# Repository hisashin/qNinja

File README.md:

# Open Source $300 Real Time PCR and LAMP machine "qNinja"

# $50 qLAMP machine "[qNinja Lite](https://github.com/hisashin/qNinjaLite)" is also available

## Reference Links
- [qNinja portal](https://qninja.hisa.dev)

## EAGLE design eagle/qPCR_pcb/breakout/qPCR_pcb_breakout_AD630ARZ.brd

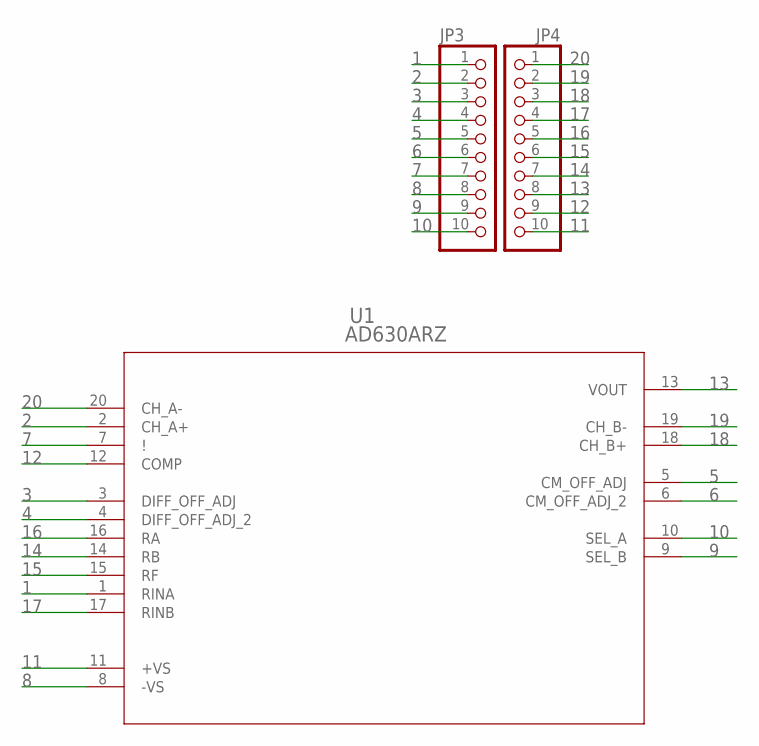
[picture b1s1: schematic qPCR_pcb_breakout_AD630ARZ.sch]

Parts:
JP3, JP4: PINHD-1X10; 1X10
U1: AD630ARZ; RW_20_ADI

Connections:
1: JP3.1, U1.1 (RINA)
2: JP3.2, U1.2 (CH_A+)
3: JP3.3, U1.3 (DIFF_OFF_ADJ)
4: JP3.4, U1.4 (DIFF_OFF_ADJ_2)
5: JP3.5, U1.5 (CM_OFF_ADJ)
6: JP3.6, U1.6 (CM_OFF_ADJ_2)
7: JP3.7, U1.7 (!)
8: JP3.8, U1.8 (-VS)
9: JP3.9, U1.9 (SEL_B)
10: JP3.10, U1.10 (SEL_A)
11: JP4.10, U1.11 (+VS)
12: JP4.9, U1.12 (COMP)
13: JP4.8, U1.13 (VOUT)
14: JP4.7, U1.14 (RB)
15: JP4.6, U1.15 (RF)
16: JP4.5, U1.16 (RA)
17: JP4.4, U1.17 (RINB)
18: JP4.3, U1.18 (CH_B+)
19: JP4.2, U1.19 (CH_B-)
20: JP4.1, U1.20 (CH_A-)

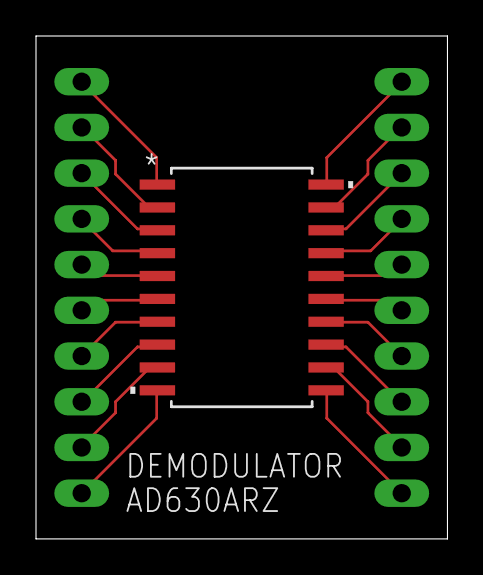
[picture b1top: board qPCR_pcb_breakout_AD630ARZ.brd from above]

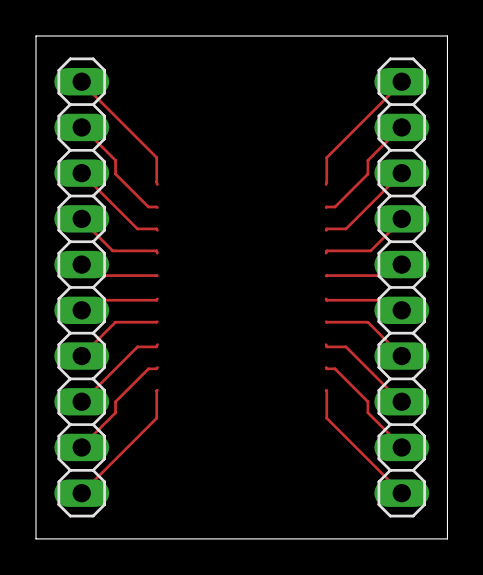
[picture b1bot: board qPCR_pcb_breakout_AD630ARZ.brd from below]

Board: 2 copper layers, 22.9 x 27.9 mm, 3 parts (2 on the bottom side), 20 nets.

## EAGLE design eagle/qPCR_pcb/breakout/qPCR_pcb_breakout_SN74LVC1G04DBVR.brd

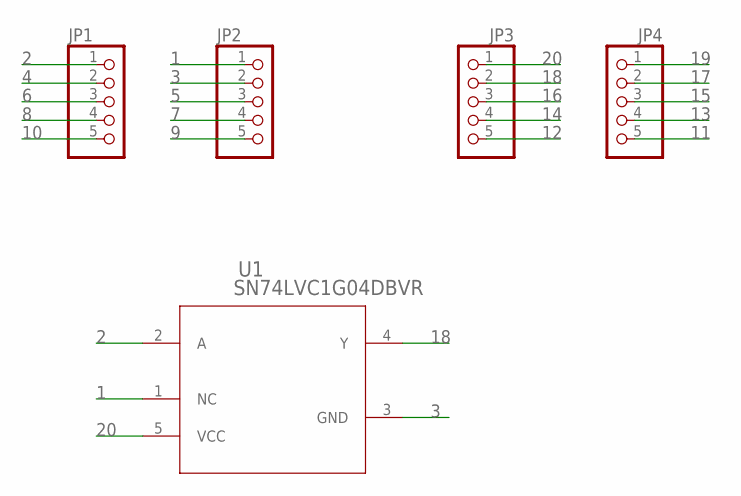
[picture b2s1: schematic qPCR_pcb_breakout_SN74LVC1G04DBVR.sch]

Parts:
JP1, JP2, JP3, JP4: PINHD-1X5R; 1X05R
U1: SN74LVC1G04DBVR; DBV5

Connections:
1: JP2.1, U1.1 (NC)
2: JP1.1, U1.2 (A)
3: JP2.2, U1.3 (GND)
4: JP1.2
5: JP2.3
6: JP1.3
7: JP2.4
8: JP1.4
9: JP2.5
10: JP1.5
11: JP4.5
12: JP3.5
13: JP4.4
14: JP3.4
15: JP4.3
16: JP3.3
17: JP4.2
18: JP3.2, U1.4 (Y)
19: JP4.1
20: JP3.1, U1.5 (VCC)

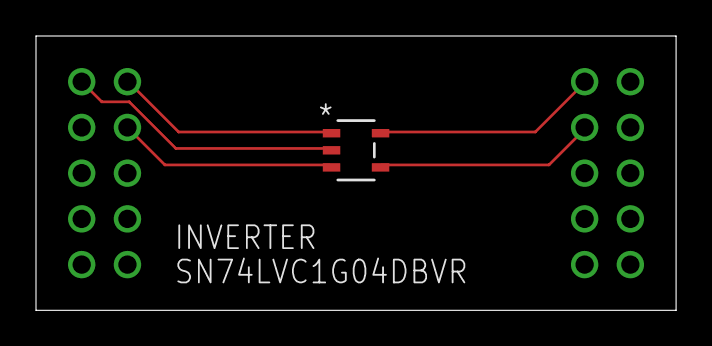
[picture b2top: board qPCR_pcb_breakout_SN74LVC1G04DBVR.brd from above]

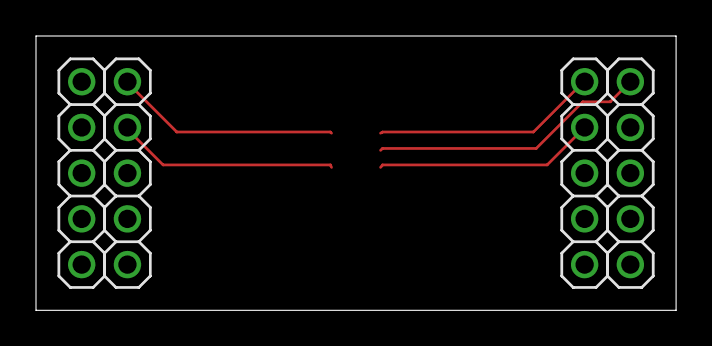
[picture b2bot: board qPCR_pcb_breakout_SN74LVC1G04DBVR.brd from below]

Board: 2 copper layers, 35.6 x 15.2 mm, 5 parts (4 on the bottom side), 5 nets.

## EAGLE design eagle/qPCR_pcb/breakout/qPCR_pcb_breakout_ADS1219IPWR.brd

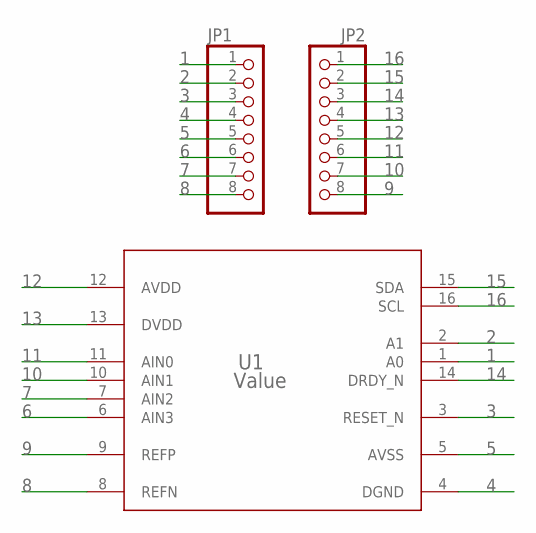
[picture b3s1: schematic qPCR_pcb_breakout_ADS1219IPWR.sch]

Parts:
JP1, JP2: PINHD-1X8; 1X08
U1: Value; PW0016A_N

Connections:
1: JP1.1, U1.1 (A0)
2: JP1.2, U1.2 (A1)
3: JP1.3, U1.3 (RESET_N)
4: JP1.4, U1.4 (DGND)
5: JP1.5, U1.5 (AVSS)
6: JP1.6, U1.6 (AIN3)
7: JP1.7, U1.7 (AIN2)
8: JP1.8, U1.8 (REFN)
9: JP2.8, U1.9 (REFP)
10: JP2.7, U1.10 (AIN1)
11: JP2.6, U1.11 (AIN0)
12: JP2.5, U1.12 (AVDD)
13: JP2.4, U1.13 (DVDD)
14: JP2.3, U1.14 (DRDY_N)
15: JP2.2, U1.15 (SDA)
16: JP2.1, U1.16 (SCL)

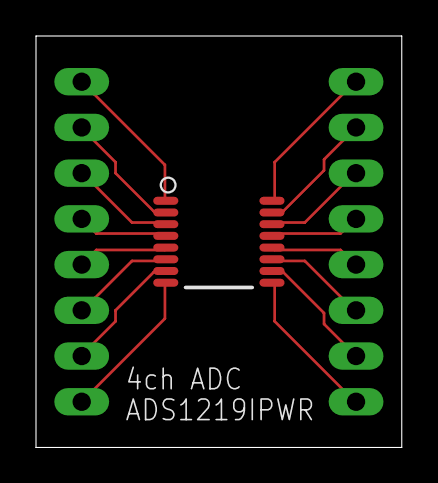
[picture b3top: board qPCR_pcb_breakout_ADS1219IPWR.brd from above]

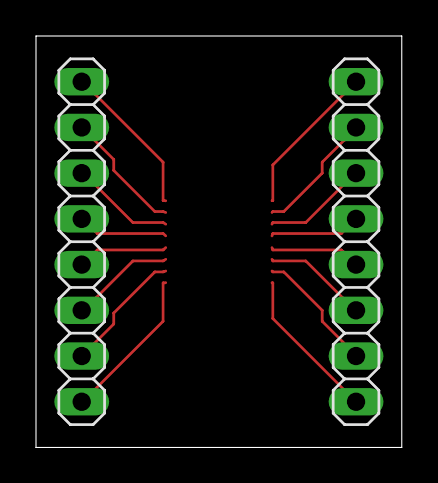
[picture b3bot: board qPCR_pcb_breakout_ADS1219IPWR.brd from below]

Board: 2 copper layers, 20.3 x 22.9 mm, 3 parts (2 on the bottom side), 16 nets.

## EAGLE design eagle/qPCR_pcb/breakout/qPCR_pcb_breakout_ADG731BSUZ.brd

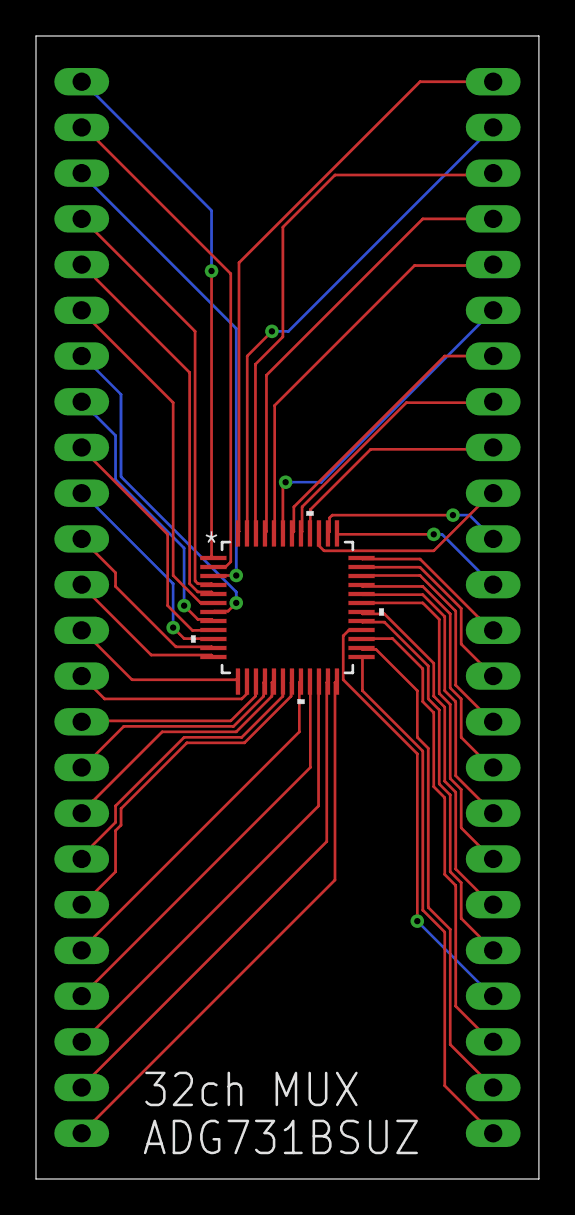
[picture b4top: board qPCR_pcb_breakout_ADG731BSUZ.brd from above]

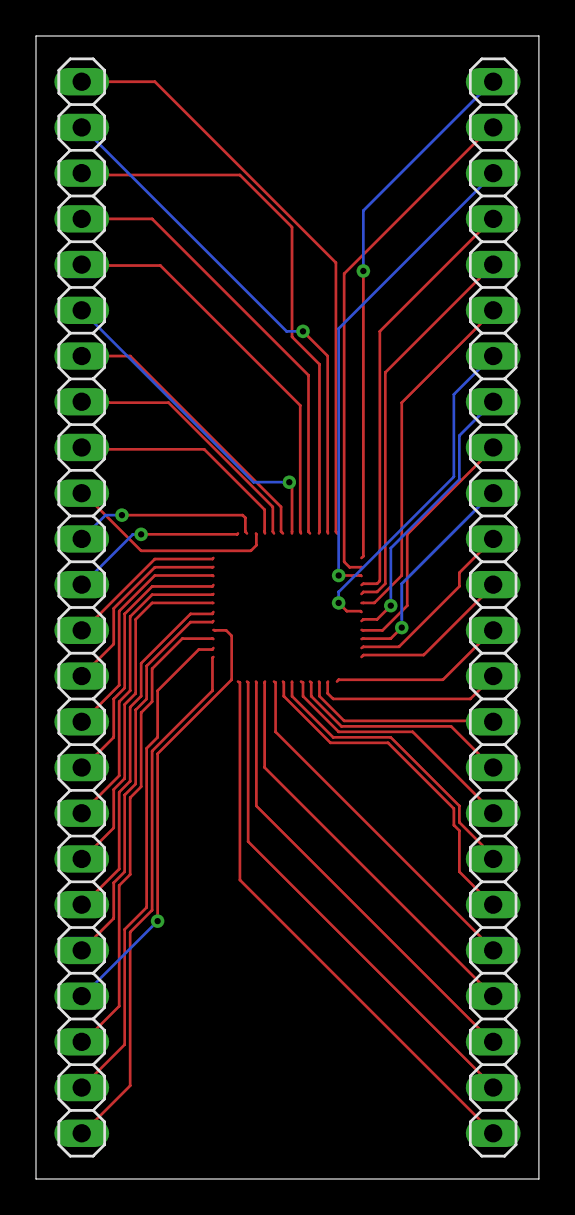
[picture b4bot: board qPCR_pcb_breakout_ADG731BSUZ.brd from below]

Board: 2 copper layers, 27.9 x 63.5 mm, 3 parts (2 on the bottom side), 48 nets.

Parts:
JP1, JP2: 1X24
U1: ADG731BSUZ; SU_48_ADI

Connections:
1: JP1.1, U1.1
2: JP1.2, U1.2
3: JP1.3, U1.3
4: JP1.4, U1.4
5: JP1.5, U1.5
6: JP1.6, U1.6
7: JP1.7, U1.7
8: JP1.8, U1.8
9: JP1.9, U1.9
10: JP1.10, U1.10
11: JP1.11, U1.11
12: JP1.12, U1.12
13: JP1.13, U1.13
14: JP1.14, U1.14
15: JP1.15, U1.15
16: JP1.16, U1.16
17: JP1.17, U1.17
18: JP1.18, U1.18
19: JP1.19, U1.19
20: JP1.20, U1.20
21: JP1.21, U1.21
22: JP1.22, U1.22
23: JP1.23, U1.23
24: JP1.24, U1.24
25: JP2.24, U1.25
26: JP2.23, U1.26
27: JP2.22, U1.27
28: JP2.21, U1.28
29: JP2.20, U1.29
30: JP2.19, U1.30
31: JP2.18, U1.31
32: JP2.17, U1.32
33: JP2.16, U1.33
34: JP2.15, U1.34
35: JP2.14, U1.35
36: JP2.13, U1.36
37: JP2.12, U1.37
38: JP2.11, U1.38
39: JP2.10, U1.39
40: JP2.9, U1.40
41: JP2.8, U1.41
42: JP2.7, U1.42
43: JP2.6, U1.43
44: JP2.5, U1.44
45: JP2.4, U1.45
46: JP2.3, U1.46
47: JP2.2, U1.47
48: JP2.1, U1.48

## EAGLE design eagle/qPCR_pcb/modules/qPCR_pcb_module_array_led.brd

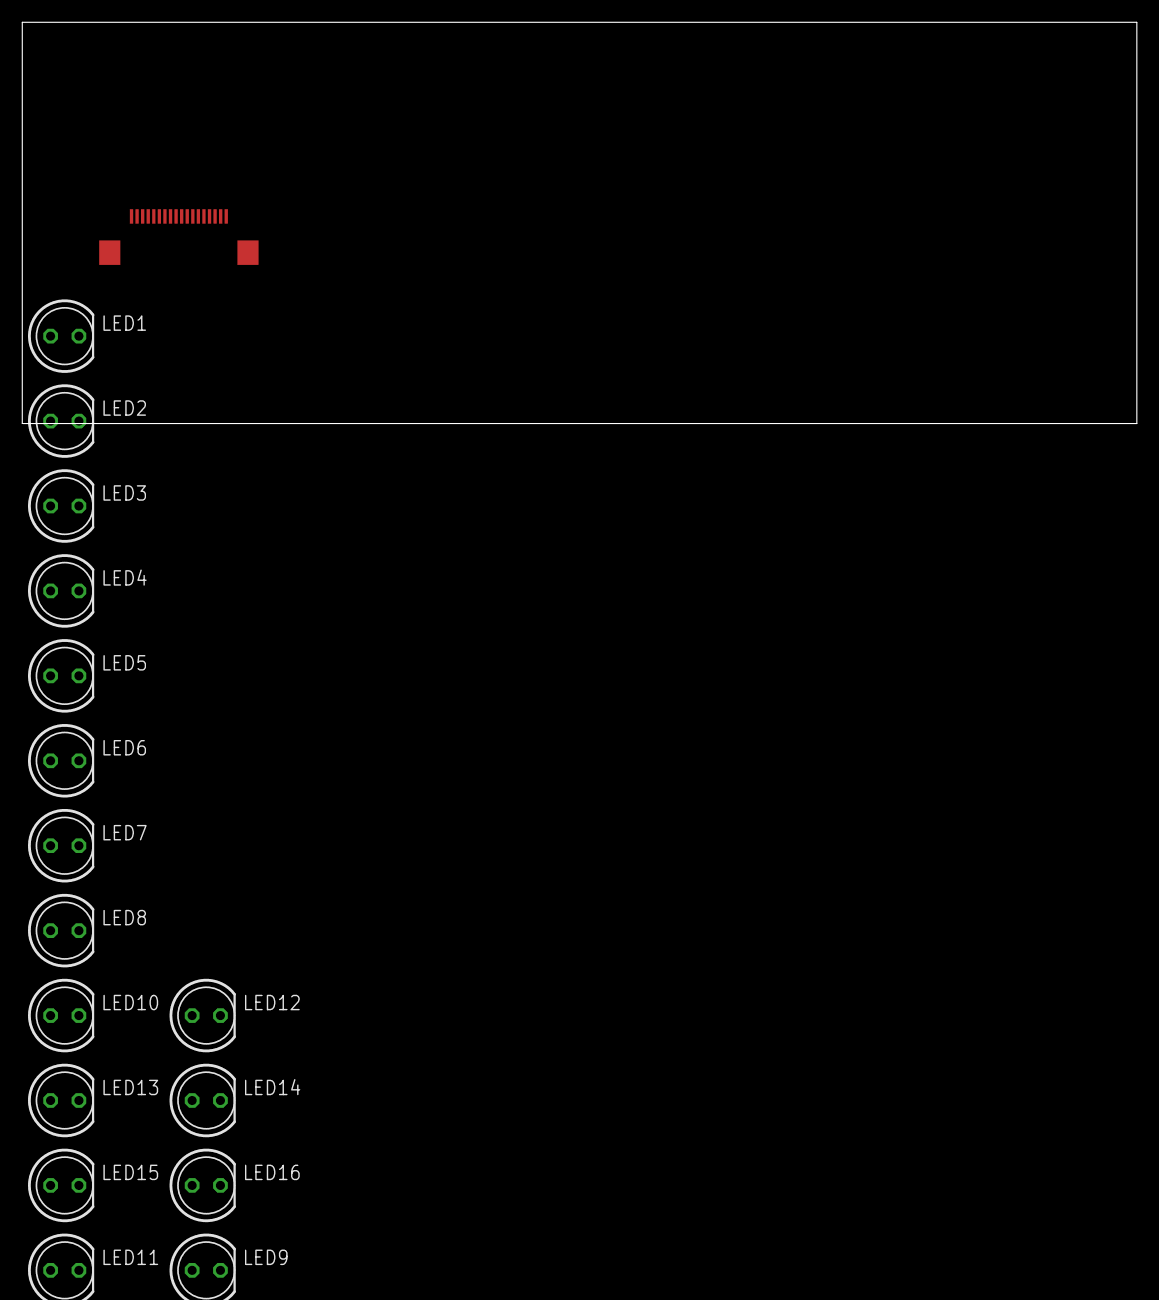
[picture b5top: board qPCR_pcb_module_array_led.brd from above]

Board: 2 copper layers, 100.0 x 36.0 mm, 17 parts (0 on the bottom side), 18 nets, no tracks yet.

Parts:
LED1, LED2, LED3, LED4, LED5, LED6, LED7, LED8, LED9, LED10, LED11, LED12, LED13, LED14, LED15, LED16: LED5MM
U$1: TF31-18S-0.5SH(800)

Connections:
5V: LED1.A, LED2.A, LED3.A, LED4.A, LED5.A, LED6.A, LED7.A, LED8.A, LED9.A, LED10.A, LED11.A, LED12.A, LED13.A, LED14.A, LED15.A, LED16.A, U$1.P$1
GND: U$1.EPAD1, U$1.EPAD2, U$1.P$18
OUT1: LED1.K, U$1.P$2
OUT2: LED2.K, U$1.P$3
OUT3: LED3.K, U$1.P$4
OUT4: LED4.K, U$1.P$5
OUT5: LED5.K, U$1.P$6
OUT6: LED6.K, U$1.P$7
OUT7: LED7.K, U$1.P$8
OUT8: LED8.K, U$1.P$9
OUT9: LED9.K, U$1.P$10
OUT10: LED10.K, U$1.P$11
OUT11: LED11.K, U$1.P$12
OUT12: LED12.K, U$1.P$13
OUT13: LED13.K, U$1.P$14
OUT14: LED14.K, U$1.P$15
OUT15: LED15.K, U$1.P$16
OUT16: LED16.K, U$1.P$17

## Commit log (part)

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2021-04-23 Modified test code (For testing batch6 boards)
2021-04-27 batch7
2021-04-27 Connect Amp's VSS to negative bias line
2021-04-27 repanelize
2021-05-07 add pushpin
2021-05-09 Bump url-parse from 1.4.7 to 1.5.1 in /src/qpcr-console
    Bumps [url-parse](https://github.com/unshiftio/url-parse) from 1.4.7 to 1.5.1.
    - [Release notes](https://github.com/unshiftio/url-parse/releases)
    - [Commits](https://github.com/unshiftio/url-parse/compare/1.4.7...1.5.1)
2021-05-12 Bump chart.js from 2.9.3 to 2.9.4 in /src/qpcr-console
    Bumps [chart.js](https://github.com/chartjs/Chart.js) from 2.9.3 to 2.9.4.
    - [Release notes](https://github.com/chartjs/Chart.js/releases)
    - [Commits](https://github.com/chartjs/Chart.js/compare/v2.9.3...v2.9.4)
2021-05-17 set note
2021-05-18 Implement thermalcycler
2021-05-20 Implement thermistor switching
2021-05-27 Add batch8 Photosensing and Main
2021-05-27 Bump dns-packet from 1.3.1 to 1.3.4 in /src/qpcr-console
    Bumps [dns-packet](https://github.com/mafintosh/dns-packet) from 1.3.1 to 1.3.4.
    - [Release notes](https://github.com/mafintosh/dns-packet/releases)
    - [Changelog](https://github.com/mafintosh/dns-packet/blob/master/CHANGELOG.md)
    - [Commits](https://github.com/mafintosh/dns-packet/compare/v1.3.1...v1.3.4)
2021-05-28 add usd
2021-06-01 add supercap to main
2021-06-01 add con1x4 for rpi lcd
2021-06-01 Update footprint lib
2021-06-03 abstract layout
2021-06-03 add keepout
2021-06-03 Add library
2021-06-03 Add tact switch / Replace thermistor MUX
2021-06-04 remove unnecessary R
2021-06-04 remove cheapest LCD and tacts
2021-06-07 add zero
2021-06-08 add PCA995B library
2021-06-08 Add sub schematics
2021-06-08 update net
2021-06-09 Add PCA9955B library
2021-06-10 Update library
    * Add TS12A12511DCNR (analog switch)
    * Add 74HC4067PW118 (Analog MUX)
2021-06-10 Replace ADC
2021-06-10 Replace gain switch, OpAmp, MUX and ADC
2021-06-10 Add ADC capacitor
2021-06-10 ADS122C04IPWR library
2021-06-11 Add MUX_8ch
2021-06-11 layout
2021-06-14 Implemented batch8 software
2021-06-15 Thermistor switching
2021-06-16 Remove SPI from batch8 hardware controller
2021-06-16 Update pin definition
2021-06-16 Define ADC channels
2021-06-16 wire
2021-06-17 wire and rename to root
2021-06-17 Artwork of root board
2021-06-17 push
2021-06-17 Replace connector on root board
2021-06-17 Create groups on photosensing board
2021-06-18 Update photosensing artwork
2021-06-18 change footprints
2021-06-20 Update photosensing board / replace thermistor connectors
2021-06-22 cleanup
2021-06-22 Associate 3d models
2021-06-22 cleanup root
2021-06-22 move R8&9
2021-06-23 Add pin socket
2021-06-23 add M3 hole to ps
2021-06-23 add 2x20 socket
2021-06-29 order batch8
2021-06-29 Bump color-string from 1.5.3 to 1.5.5 in /src/qpcr-console
    Bumps [color-string](https://github.com/Qix-/color-string) from 1.5.3 to 1.5.5.
    - [Release notes](https://github.com/Qix-/color-string/releases)
    - [Changelog](https://github.com/Qix-/color-string/blob/master/CHANGELOG.md)
    - [Commits](https://github.com/Qix-/color-string/commits/1.5.5)
    ---
    updated-dependencies:
2021-07-02 Update styles for Kiosk mode
2021-07-07 add stl
2021-07-07 add stls
2021-07-09 update airflow
2021-07-15 Update layout
2021-07-22 Update ADC & LED driver
2021-07-22 Add LED & thermistor demo code
2021-07-28 Update experiment manager
2021-07-28 add ezcad fiber laser data to cut filters
2021-07-29 add spectrum graph
2021-08-05 Update pub/sub library / Add debug interface / shutdown device safely on SIGINT
2021-08-24 add batch9
2021-08-24 Add AOZ6663DI library
2021-08-24 Revert "Add AOZ6663DI library"
    This reverts commit e73cb10a9f4ee7b6da734098bee8f617061be07d.
2021-08-24 Revert "Revert "Add AOZ6663DI library""
    This reverts commit a7c1f28a366411bddff9f81c7c3bc76965d433cd.
2021-08-24 Add 5V generation board's schematic
2021-08-25 size
2021-08-25 update optics
2021-08-25 add -1v
2021-08-26 Add negative voltage files
2021-08-26 -1V board artwork
2021-08-27 Update 5V board
2021-08-30 batch9
2021-08-30 add photo-single/dual
2021-08-31 correct led
2021-08-31 wire 5v
2021-08-31 Add BD9D323QWZ-E2 footprint library
2021-08-31 Add temperature monitoring class
2021-08-31 add break
2021-08-31 Update packaging document (added description about shutdown button)
2021-09-01 Add packaging manual
2021-09-01 detail panel
2021-09-03 Updated progress monitor
2021-09-05 Fix dashboard reload problem
2021-09-07 change value
2021-09-07 Add radio buttons to specify data collection timing
2021-09-08 memo
2021-09-08 Update kiosk-mode UI
2021-09-21 initialize main
2021-09-21 init batch10/main
2021-09-21 Enable resistor switching (temperature measurement)
2021-09-21 Bump tmpl from 1.0.4 to 1.0.5 in /src/qpcr-console
    Bumps [tmpl](https://github.com/daaku/nodejs-tmpl) from 1.0.4 to 1.0.5.
    - [Release notes](https://github.com/daaku/nodejs-tmpl/releases)
    - [Commits](https://github.com/daaku/nodejs-tmpl/commits/v1.0.5)
    ---
    updated-dependencies:
    - dependency-name: tmpl
2021-09-22 Fixed date format of experiment template
2021-09-22 Abort -> Cancel (This command may be called before starting)
2021-09-24 replace parts in stock
2021-09-25 Update styles
2021-09-29 Updated layout wireframe
2021-09-29 wire batch10/main
2021-09-30 ordered batch10
2021-10-01 with/without peltier
2021-10-01 stop relay
2021-10-02 initialize batch11
2021-10-05 Add peltier control board
2021-10-05 Updated peltier board
2021-10-05 update paste
2021-10-05 Added barrel jack
2021-10-06 Peltier test board is almost complete
2021-10-07 ordered breakouts01+02
2021-10-08 add relay
2021-10-08 pel+rel
2021-10-08 wire pel+rel
2021-10-11 Implemented Peltier control for batch11
2021-10-21 main/peltier+relay soldered
2021-10-26 add peltier+relay
2021-10-26 remove unused
2021-10-29 Updated switching regulator circuit
2021-11-12 init batch14/main
2021-11-18 Update network settings system
2021-11-24 Copy peltier+relay
2021-11-24 Added parts memo
2021-11-24 Update schematic / Add footprint
2021-11-25 Added SRP1265C footprint
2021-11-25 Update batch14 artwork
2021-12-01 Update manual / Update PWM test code
2021-12-01 Add batch15 peltier+relay file (just copied from batch14)
2021-12-02 move batch14/main to batch15/main
2021-12-03 Added 2 footprints
2021-12-06 ordered batch15/main
2021-12-07 Add batch15 hardware control
2021-12-15 soldered batch15/main
2021-12-20 add batch18/main
2022-01-14 Bump follow-redirects from 1.13.0 to 1.14.7 in /src/qpcr-console
    Bumps [follow-redirects](https://github.com/follow-redirects/follow-redirects) from 1.13.0 to 1.14.7.
    - [Release notes](https://github.com/follow-redirects/follow-redirects/releases)
    - [Commits](https://github.com/follow-redirects/follow-redirects/compare/v1.13.0...v1.14.7)
    ---
    updated-dependencies:
    - dependency-name: follow-redirects
2022-01-27 minor fixes onto batch18/main
2022-02-13 Bump follow-redirects from 1.13.0 to 1.14.8 in /src/qpcr-console
    Bumps [follow-redirects](https://github.com/follow-redirects/follow-redirects) from 1.13.0 to 1.14.8.
    - [Release notes](https://github.com/follow-redirects/follow-redirects/releases)
    - [Commits](https://github.com/follow-redirects/follow-redirects/compare/v1.13.0...v1.14.8)
    ---
    updated-dependencies:
    - dependency-name: follow-redirects
2022-02-16 Updated console
2022-02-17 Update UI
2022-02-20 wired
2022-02-23 wire led
2022-02-24 ordered batch18/main
2022-02-25 Update UI / PID tuning
2022-02-27 Bump url-parse from 1.4.7 to 1.5.10 in /src/qpcr-console
    Bumps [url-parse](https://github.com/unshiftio/url-parse) from 1.4.7 to 1.5.10.
    - [Release notes](https://github.com/unshiftio/url-parse/releases)
    - [Commits](https://github.com/unshiftio/url-parse/compare/1.4.7...1.5.10)
    ---
    updated-dependencies:
    - dependency-name: url-parse
2022-03-09 Control intensity of LED by setting IREF value
2022-03-26 Bump minimist from 1.2.5 to 1.2.6 in /src/qpcr-console
    Bumps [minimist](https://github.com/substack/minimist) from 1.2.5 to 1.2.6.
    - [Release notes](https://github.com/substack/minimist/releases)
    - [Commits](https://github.com/substack/minimist/compare/1.2.5...1.2.6)
    ---
    updated-dependencies:
    - dependency-name: minimist
2022-03-29 Fix transition bug (Properly process empty strings in protocol.json)
2022-04-29 Bump async from 2.6.3 to 2.6.4 in /src/qpcr-console
    Bumps [async](https://github.com/caolan/async) from 2.6.3 to 2.6.4.
    - [Release notes](https://github.com/caolan/async/releases)
    - [Changelog](https://github.com/caolan/async/blob/v2.6.4/CHANGELOG.md)
    - [Commits](https://github.com/caolan/async/compare/v2.6.3...v2.6.4)
    ---
    updated-dependencies:
2022-06-01 Bump eventsource from 1.0.7 to 1.1.1 in /src/qpcr-console
    Bumps [eventsource](https://github.com/EventSource/eventsource) from 1.0.7 to 1.1.1.
    - [Release notes](https://github.com/EventSource/eventsource/releases)
    - [Changelog](https://github.com/EventSource/eventsource/blob/master/HISTORY.md)
    - [Commits](https://github.com/EventSource/eventsource/compare/v1.0.7...v1.1.1)
    ---
    updated-dependencies:
2022-07-07 Bump moment from 2.27.0 to 2.29.4 in /src/qpcr-console
    Bumps [moment](https://github.com/moment/moment) from 2.27.0 to 2.29.4.
    - [Release notes](https://github.com/moment/moment/releases)
    - [Changelog](https://github.com/moment/moment/blob/develop/CHANGELOG.md)
    - [Commits](https://github.com/moment/moment/compare/2.27.0...2.29.4)
    ---
    updated-dependencies:
2022-07-21 Bump terser from 4.6.12 to 4.8.1 in /src/qpcr-console
    Bumps [terser](https://github.com/terser/terser) from 4.6.12 to 4.8.1.
    - [Release notes](https://github.com/terser/terser/releases)
    - [Changelog](https://github.com/terser/terser/blob/master/CHANGELOG.md)
    - [Commits](https://github.com/terser/terser/commits)
    ---
    updated-dependencies:
2022-08-16 apply changes from Lite
2022-08-19 batch03/main wiring
2022-08-22 wired batch18/main
2022-08-22 just before wiring photo-(single|dual)
2022-08-24 batch18/photo-(single|dual) ready to order
2022-10-18 import amp changes from qNinjaLite/batch04 to batch19/main
2022-11-02 Bump lodash from 4.17.15 to 4.17.21 in /src/server
    Bumps [lodash](https://github.com/lodash/lodash) from 4.17.15 to 4.17.21.
    - [Release notes](https://github.com/lodash/lodash/releases)
    - [Commits](https://github.com/lodash/lodash/compare/4.17.15...4.17.21)
    ---
    updated-dependencies:
    - dependency-name: lodash
2022-11-02 Bump ws from 6.2.1 to 6.2.2 in /src/server
    Bumps [ws](https://github.com/websockets/ws) from 6.2.1 to 6.2.2.
    - [Release notes](https://github.com/websockets/ws/releases)
    - [Commits](https://github.com/websockets/ws/compare/6.2.1...6.2.2)
    ---
    updated-dependencies:
    - dependency-name: ws
2022-11-02 Bump color-string from 1.5.3 to 1.9.1 in /src/server
    Bumps [color-string](https://github.com/Qix-/color-string) from 1.5.3 to 1.9.1.
    - [Release notes](https://github.com/Qix-/color-string/releases)
    - [Changelog](https://github.com/Qix-/color-string/blob/master/CHANGELOG.md)
    - [Commits](https://github.com/Qix-/color-string/commits/1.9.1)
    ---
    updated-dependencies:
2022-11-03 stop autodeploy
2022-11-10 wired batch19/photo-dual
2022-12-05 Bump decode-uri-component from 0.2.0 to 0.2.2 in /src/qpcr-console
    Bumps [decode-uri-component](https://github.com/SamVerschueren/decode-uri-component) from 0.2.0 to 0.2.2.
    - [Release notes](https://github.com/SamVerschueren/decode-uri-component/releases)
    - [Commits](https://github.com/SamVerschueren/decode-uri-component/compare/v0.2.0...v0.2.2)
    ---
    updated-dependencies:
    - dependency-name: decode-uri-component
2022-12-11 Bump qs from 6.5.2 to 6.5.3 in /src/qpcr-console
    Bumps [qs](https://github.com/ljharb/qs) from 6.5.2 to 6.5.3.
    - [Release notes](https://github.com/ljharb/qs/releases)
    - [Changelog](https://github.com/ljharb/qs/blob/main/CHANGELOG.md)
    - [Commits](https://github.com/ljharb/qs/compare/v6.5.2...v6.5.3)
    ---
    updated-dependencies:
2023-01-06 Bump json5 from 1.0.1 to 1.0.2 in /src/qpcr-console
    Bumps [json5](https://github.com/json5/json5) from 1.0.1 to 1.0.2.
    - [Release notes](https://github.com/json5/json5/releases)
    - [Changelog](https://github.com/json5/json5/blob/main/CHANGELOG.md)
    - [Commits](https://github.com/json5/json5/compare/v1.0.1...v1.0.2)
    ---
    updated-dependencies:
2023-01-18 b19 orderd
2023-02-15 use SMT 2x5 socket for leds
2023-02-21 wired b21/photo
